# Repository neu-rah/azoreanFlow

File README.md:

# AzoreanFlow is a Hot Plate Reflow Soldering 
## Project  
Hardware by Christophe Persoz on 19/01/2018  
Software by Rui Azevedo  
Licence GNU General Public License v3

## WARNING and DISCLAIMER 
This project operates with possibly lethal AC voltage. If you are unsure what to do, don't do it and get help from an experienced tinkerer with professional training and skills.  

## TODO

* Alarms
* Choosing existing profiles
* Edit profiles
* Select time or temp drive (guess i will kill temp. drive, testing)
* Machine calibration
* Ensure profile fits the machine (after callibration)
* Store profiles

## Info
#### This is an Arduino-based reflow plate controller with
* PID loop control  
* Wave Packet and Phase Fired control for AC outputs  
* Use Zero Crossing SSR
* Graphic TFT LC-Display, drawing the temperature curves using a 1.8" TFT or derivate display
* Controlled using a ~~cheap rotary encoder and its~~ single button  
* ~~Stores up to 30 temperature profiles in EEPROM~~  (not yet)
* Configurable PID-parameters (only in code)
* Simple, small hardware to drive loads up to 400V and up to 6A  
* Hardware can measure two temperatures independently drive one AC load and one DC load, such as a fan

## Main Characteristics
* 2 K-thermocouple input associated to MAX31588 HE SPI controller  
* 2 SSR output (One for Heat Plate - 6A, the other for a 12V Fan - 1A)  
* ~~Rotary encoder with switch for user input~~
* TFT 1.8" HW SPI Color display for feedback and control  
* Beeper for advertising  

~~Please Note: Requires Arduino IDE 1.5.x or newer.~~
Based on 0xPIT hardware, but contains a lot of updates on hardware and a complete new software.

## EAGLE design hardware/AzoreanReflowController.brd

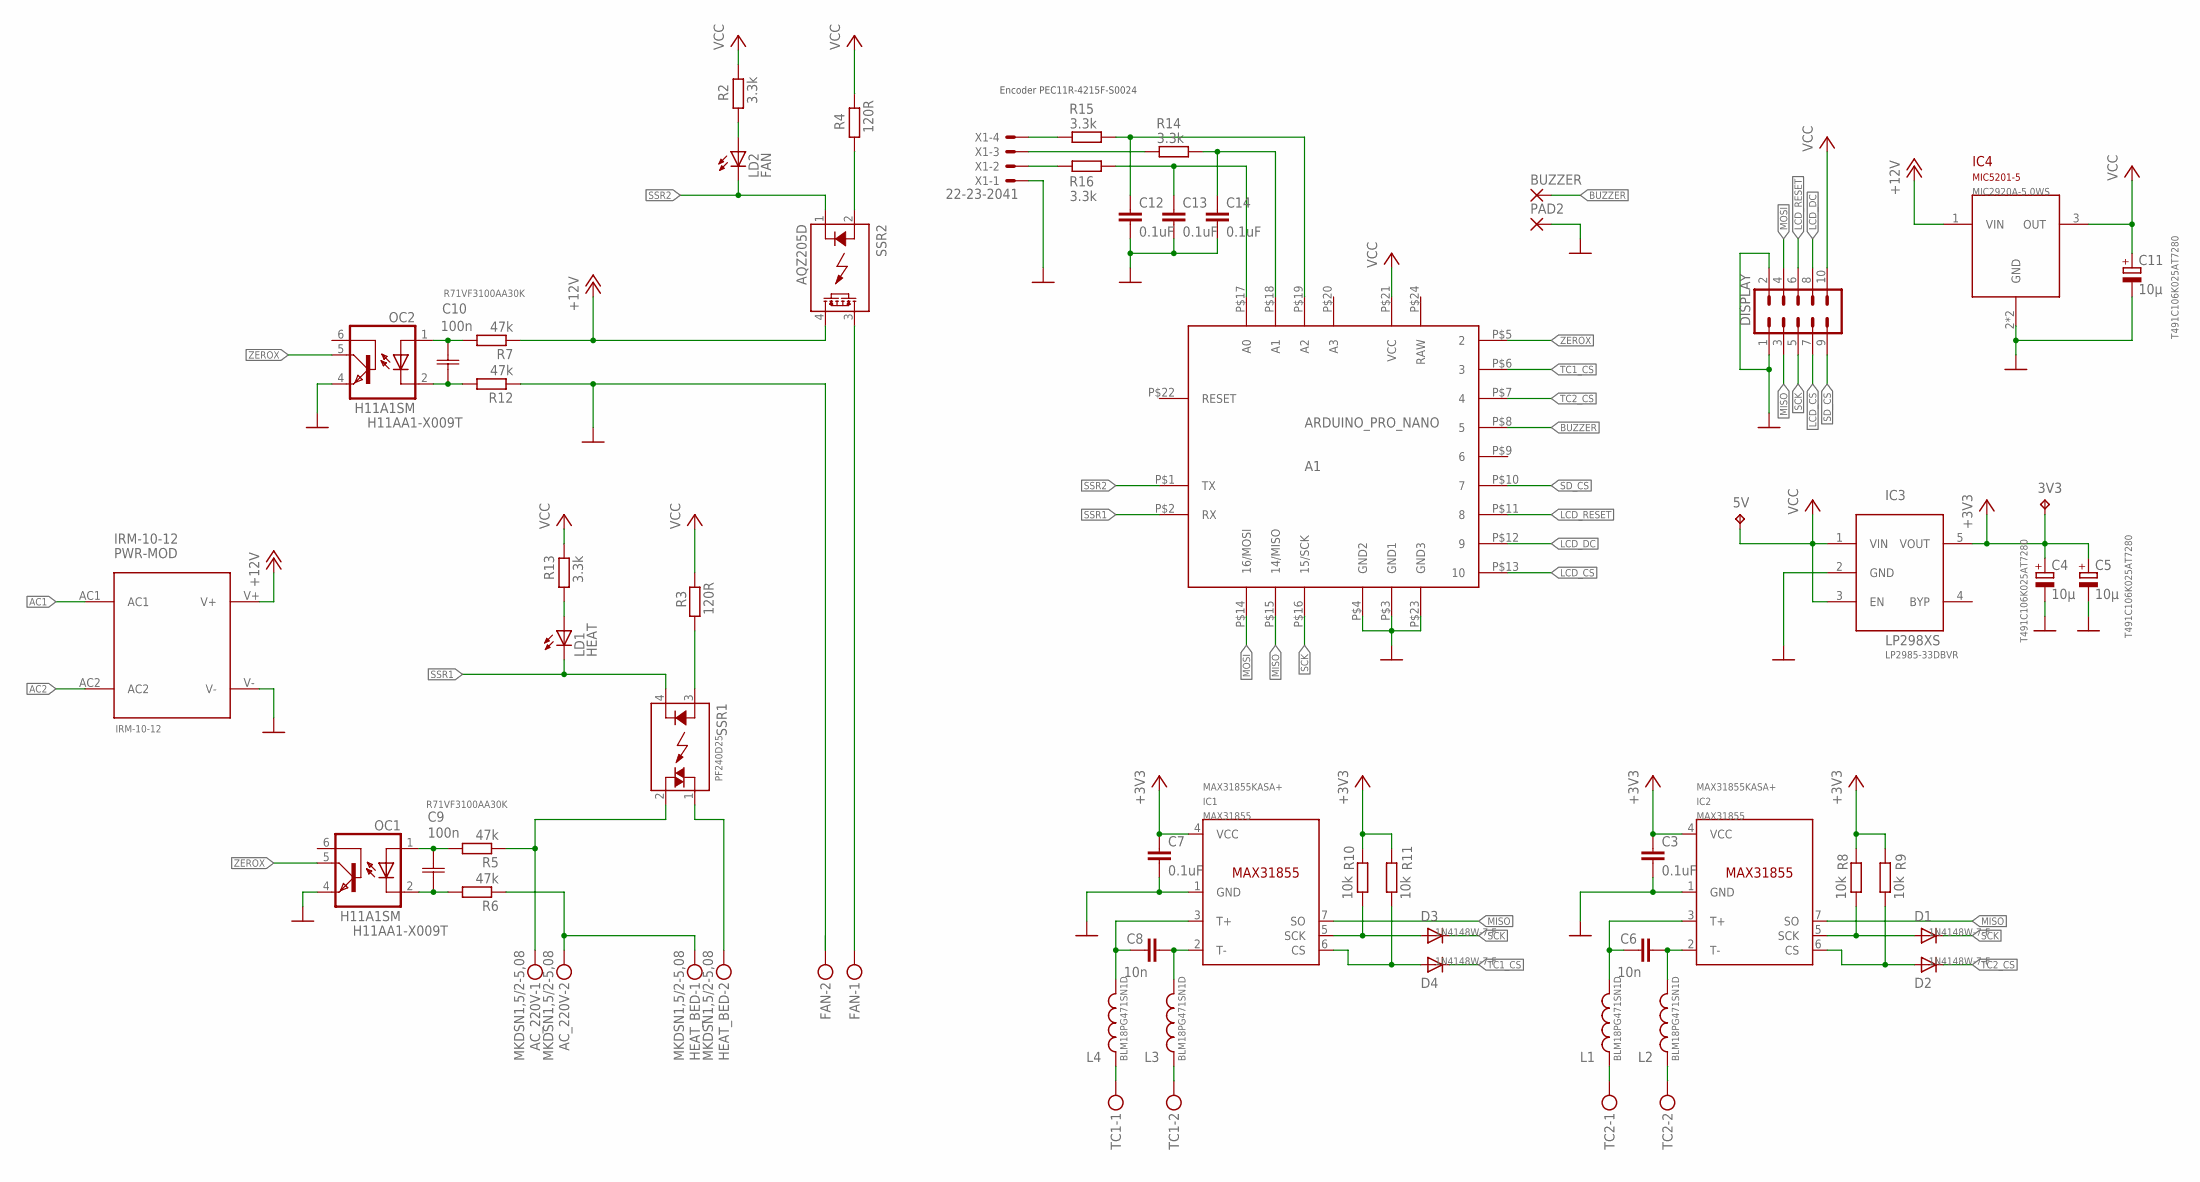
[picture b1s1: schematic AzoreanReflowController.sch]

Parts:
3V3, 5V: TPTP08R; TP08R
A1: ARDUINO_PRO_NANO
AC_220V: MKDSN1,5/2-5,08
BUZZER: 1,6/0,8
C3, C7, C12, C13, C14: 0.1uF; 0603
C4, C5, C11: 10µ; C/6032-28R
C6, C8: 10n; C0603
C9, C10: 100n; R71V
D1, D2, D3, D4: DIODESOD-123; SOD-123
DISPLAY: M05X2SHD-NS; 2X5-SHROUDED-NS
FAN: MKDSN1,5/2-5,08
HEAT_BED: MKDSN1,5/2-5,08
IC1, IC2: MAX31855; SOIC8
IC3: LP298XS; SOT23-5L
IC4: MIC5201-5; SOT-223
L1, L2, L3, L4: INDUCTOR0603; 0603
LD1: HEAT; CHIP-LED0603
LD2: FAN; CHIP-LED0603
OC1, OC2: H11A1SM; DIL6-SMD
PAD2: 1,6/0,8
PWR-MOD: IRM-10-12
R2, R13, R14, R15, R16: 3.3k; R0603
R3, R4: 120R; R0603
R5, R6, R7, R12: 47k; 0207/5V
R8, R9, R10, R11: 10k; R0603
SSR1: PF240D25; PF240XX
SSR2: AQZ205D; AQZ-SIL04
TC1, TC2: MKDSN1,5/2-5,08
X1: 22-23-2041

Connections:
12V: IC4.1 (VIN), PWR-MOD.V+, R7.1, SSR2.4 (DS2)
+3V3: 3V3.TP, C3.1, C4.+, C5.+, C7.1, IC1.4 (VCC), IC2.4 (VCC), IC3.5 (VOUT), R8.2, R9.2, R10.2, R11.2
AC1: AC_220V.1, PWR-MOD.AC1, R5.1, SSR1.2 (ACL2)
AC2: AC_220V.2, HEAT_BED.1, PWR-MOD.AC2, R6.1
AC_OUT1: HEAT_BED.2, SSR1.1 (ACL1)
BUZZER: A1.P$8 (5), BUZZER.1
FAN_OUT: FAN.1, SSR2.3 (DS1)
GND: A1.P$3 (GND1), A1.P$4 (GND2), A1.P$23 (GND3), C3.2, C4.-, C5.-, C7.2, C11.-, C12.2, C13.2, C14.2, DISPLAY.1, DISPLAY.2, FAN.2, IC1.1 (GND), IC2.1 (GND), IC3.2 (GND), IC4.2 (GND), IC4.4 (GND), OC1.4 (EMI), OC2.4 (EMI), PAD2.1, PWR-MOD.V-, R12.1, X1.1
LCD_CS: A1.P$13 (10), DISPLAY.7
LCD_DC: A1.P$12 (9), DISPLAY.8
LCD_RESET: A1.P$11 (8), DISPLAY.6
MISO: A1.P$15 (14/MISO), DISPLAY.3, IC1.7 (SO), IC2.7 (SO)
MOSI: A1.P$14 (16/MOSI), DISPLAY.4
unnamed: C8.2, IC1.2 (T-), L3.2
unnamed: C6.2, IC2.2 (T-), L2.2
unnamed: C6.1, IC2.3 (T+), L1.2
unnamed: A1.P$17 (A0), C13.1, R16.2
unnamed: A1.P$18 (A1), C14.1, R14.2
unnamed: L1.1, TC2.1
unnamed: A1.P$19 (A2), C12.1, R15.2
unnamed: C9.1, OC1.1 (A), R5.2
unnamed: C9.2, OC1.2 (C), R6.2
unnamed: C8.1, IC1.3 (T+), L4.2
unnamed: C10.1, OC2.1 (A), R7.2
unnamed: R3.2, SSR1.3 (DC+)
unnamed: R4.2, SSR2.2 (A)
unnamed: D2.A, IC2.6 (CS), R9.1
unnamed: D1.A, IC2.5 (SCK), R8.1
unnamed: D4.A, IC1.6 (CS), R11.1
unnamed: D3.A, IC1.5 (SCK), R10.1
unnamed: C10.2, OC2.2 (C), R12.2
unnamed: R16.1, X1.2
unnamed: R14.1, X1.3
unnamed: L4.1, TC1.1
unnamed: L3.1, TC1.2
unnamed: L2.1, TC2.2
unnamed: LD2.A, R2.2
unnamed: R15.1, X1.4
unnamed: LD1.A, R13.2
RAW: A1.P$24 (RAW)
SCK: A1.P$16 (15/SCK), D1.C, D3.C, DISPLAY.5
SD_CS: A1.P$10 (7), DISPLAY.9
SSR1: A1.P$2 (RX), LD1.C, SSR1.4 (DC-)
SSR2: A1.P$1 (TX), LD2.C, SSR2.1 (K)
TC1_CS: A1.P$6 (3), D4.C
TC2_CS: A1.P$7 (4), D2.C
VCC: 5V.TP, A1.P$21 (VCC), C11.+, DISPLAY.10, IC3.1 (VIN), IC3.3 (EN), IC4.3 (OUT), R2.1, R3.1, R4.1, R13.1
ZEROX: A1.P$5 (2), OC1.5 (COL), OC2.5 (COL)

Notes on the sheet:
Encoder PEC11R-4215F-S0024

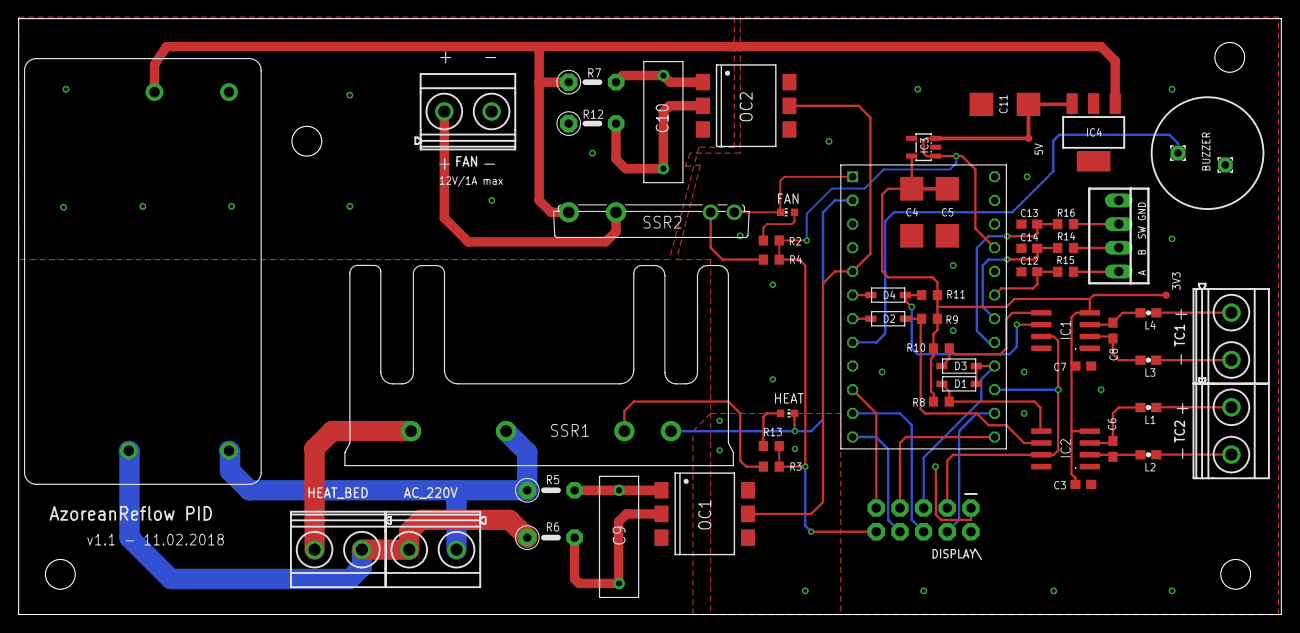
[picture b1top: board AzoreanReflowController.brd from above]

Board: 2 copper layers, 135.6 x 64.0 mm, 58 parts (0 on the bottom side), 47 nets.

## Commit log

2018-02-11 first push
2018-02-11 typo
2018-02-11 docs
2018-02-11 Add Hardware
    Add PCB, schematics and BOM for AzoreanFlow
2018-04-09 Update for DEBUG
    Now serial output is optional by activating #define DEBUG
2018-04-09 Add some beep on specific actions

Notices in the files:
parts and their libraries:
SparkFun-Capacitors: Licensing: Creative Commons ShareAlike 4.0 International - https://creativecommons.org/licenses/by-sa/4.0
